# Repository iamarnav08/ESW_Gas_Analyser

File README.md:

# ESW-Beyond_Infinity

ESW Project

## Working of MQ 2 sensor

Gases - LPG , CO , smoke

Concentration -> 30 - 500 ppm

Donor atoms (or oxygen vacancies) provide free electrons that can conduct electricity in the tin dioxide.
When the sensor is exposed to air, oxygen gets adsorbed on the surface and traps these donor electrons, reducing conductivity (increasing resistance).
When reducing gases (like methane or CO) are present, they react with the adsorbed oxygen, freeing the donor electrons and increasing the conductivity (lowering resistance).
The sensor measures these changes in resistance (conductivity), and the output voltage increases with the gas concentration because more electrons are available to flow as current.

## Working of MQ7 sensor

The MQ-7 sensor is designed to detect carbon monoxide (CO) using a tin dioxide (SnO₂) sensing element. It works by changing its electrical resistance when CO is present. In clean air, the sensor has high resistance, but when CO interacts with the SnO₂ surface, the resistance decreases.

A key feature of the MQ-7 is its cyclic heating process:

At high temperature (320°C), the sensor cleans itself by adsorbing oxygen molecules.
At low temperature (100°C), the sensor becomes sensitive to CO, reducing its resistance in the presence of CO.
The sensor outputs an analog signal proportional to the CO concentration, making it ideal for CO detectors due to its improved accuracy and selectivity.

## Specialized for CO Detection

MQ-7 is specifically designed to detect carbon monoxide (CO) with high sensitivity. It is fine-tuned through its cyclic heating process, which improves its selectivity for CO and helps reduce interference from other gases. The MQ-7 sensor employs a cyclic heating process, alternating between a high temperature (for cleaning) and a low temperature (for CO detection). This process makes the MQ-7 more selective to CO, reducing false positives from other gases like hydrogen or methane.
The MQ-7 sensor operates on a cyclic heating mechanism with two distinct temperature phases:

High-temperature phase (around 300°C to 350°C): During this phase, the sensor burns off impurities or other gases that may have adsorbed on the surface, ensuring that it is primed for CO detection.
Low-temperature phase (around 100°C to 150°C): This lower temperature is where CO is effectively detected. At this temperature, the CO molecules are adsorbed onto the SnO₂ surface, triggering the redox reaction and thus leading to a measurable change in resistance.

This temperature cycling is essential because it optimizes the sensor's selectivity for CO while minimizing interference from other gases.
Change in Electrical Resistance

## Change in electrical Resistance

As CO is oxidized on the SnO₂ surface, oxygen molecules that were previously adsorbed on the surface as O⁻ ions are released, leading to a reduction in the number of charge carriers trapped on the surface.
This release of oxygen increases the availability of free electrons in the SnO₂ material, leading to a decrease in resistance.
The change in resistance is directly proportional to the concentration of CO in the surrounding air, allowing the sensor to measure CO levels.

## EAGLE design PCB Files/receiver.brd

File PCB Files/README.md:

PCBs designed for this product.

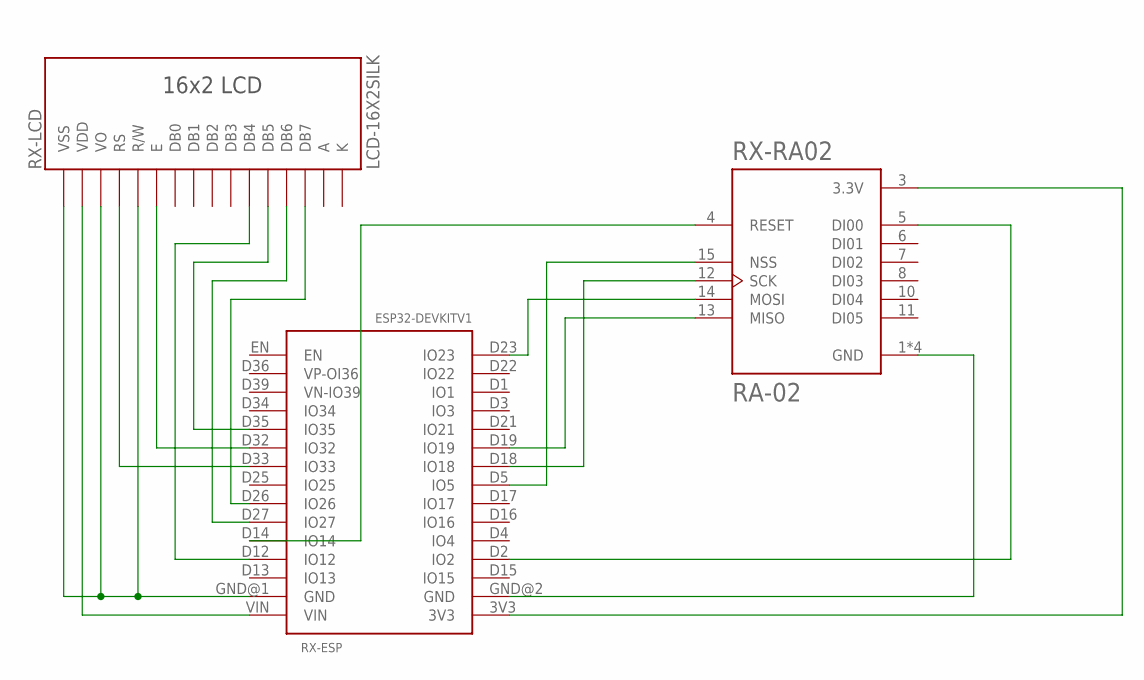
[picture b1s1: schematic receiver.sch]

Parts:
RX-ESP: ESP32DEVKITV1; ESP32-DEVKITV1
RX-LCD: LCD-16X2SILK; MODULE_LCD-16X2
RX-RA02: RA-02

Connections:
A: RX-LCD.15 (A)
K: RX-LCD.16 (K)
unnamed: RX-ESP.D23 (IO23), RX-RA02.14 (MOSI)
unnamed: RX-ESP.D2 (IO2), RX-RA02.5 (DI00)
unnamed: RX-ESP.GND@2 (GND), RX-RA02.1 (GND), RX-RA02.2 (GND), RX-RA02.9 (GND), RX-RA02.16 (GND)
unnamed: RX-ESP.D19 (IO19), RX-RA02.13 (MISO)
unnamed: RX-ESP.D18 (IO18), RX-RA02.12 (SCK)
unnamed: RX-ESP.D5 (IO5), RX-RA02.15 (NSS)
unnamed: RX-ESP.D14 (IO14), RX-RA02.4 (RESET)
unnamed: RX-ESP.3V3, RX-RA02.3 (3.3V)
unnamed: RX-ESP.VIN, RX-LCD.2 (VDD)
unnamed: RX-ESP.D32 (IO32), RX-LCD.6 (E)
unnamed: RX-ESP.D33 (IO33), RX-LCD.4 (RS)
unnamed: RX-ESP.D27 (IO27), RX-LCD.13 (DB6)
unnamed: RX-ESP.D35 (IO35), RX-LCD.12 (DB5)
unnamed: RX-ESP.D12 (IO12), RX-LCD.11 (DB4)
RX-N$1: RX-ESP.D26 (IO26), RX-LCD.14 (DB7)
RX-N$4: RX-ESP.GND@1 (GND), RX-LCD.1 (VSS), RX-LCD.3 (VO), RX-LCD.5 (R/W)

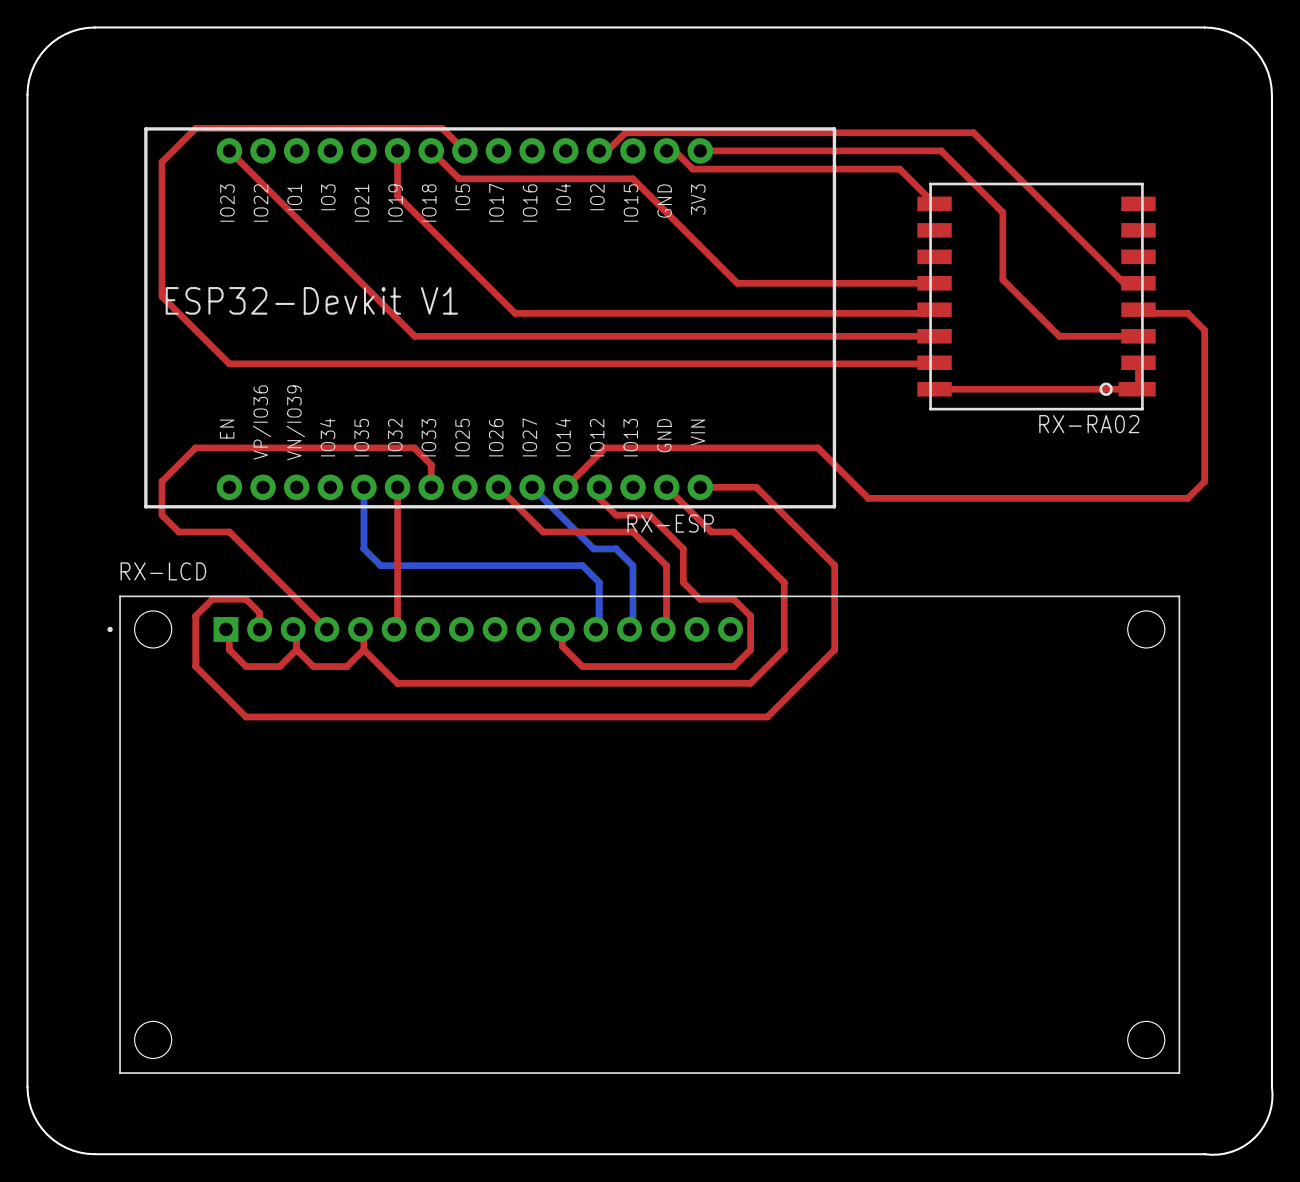
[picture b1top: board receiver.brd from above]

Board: 2 copper layers, 94.0 x 85.1 mm, 3 parts (0 on the bottom side), 16 nets.

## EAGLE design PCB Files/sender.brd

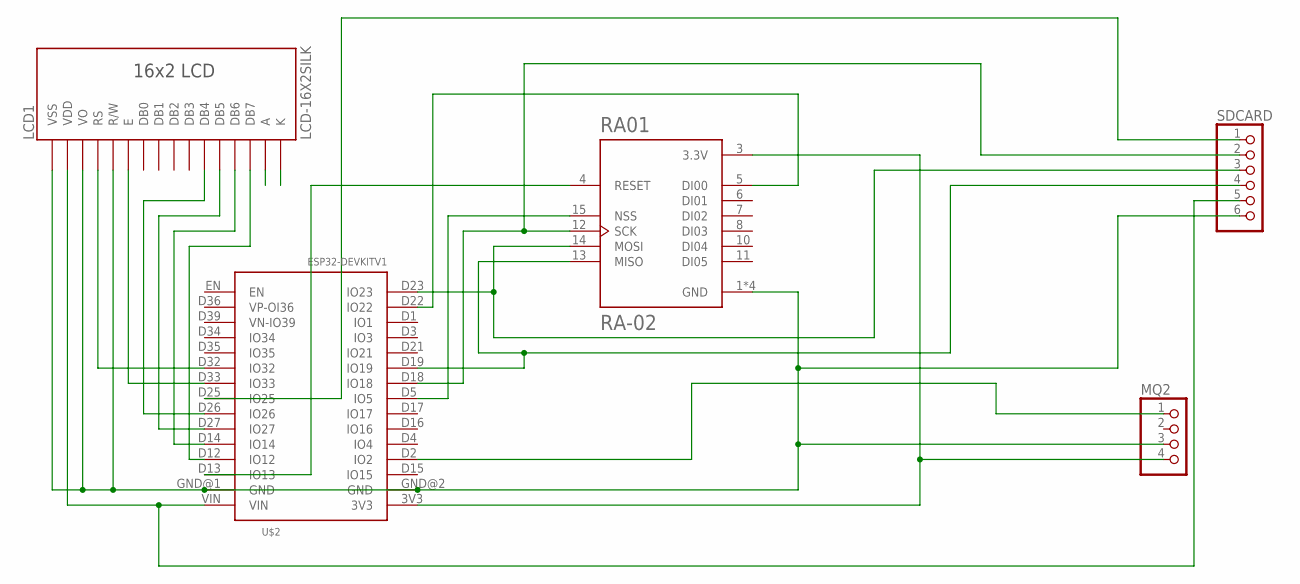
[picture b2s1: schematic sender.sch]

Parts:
LCD1: LCD-16X2SILK; MODULE_LCD-16X2
MQ2: PINHD-1X4; 1X04
RA01: RA-02
SDCARD: PINHD-1X6; 1X06
U$2: ESP32DEVKITV1; ESP32-DEVKITV1

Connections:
unnamed: RA01.4 (RESET), U$2.D13 (IO13)
unnamed: RA01.12 (SCK), SDCARD.2, U$2.D18 (IO18)
unnamed: RA01.15 (NSS), U$2.D5 (IO5)
unnamed: RA01.5 (DI00), U$2.D22 (IO22)
unnamed: RA01.13 (MISO), SDCARD.4, U$2.D19 (IO19)
unnamed: RA01.14 (MOSI), SDCARD.3, U$2.D23 (IO23)
unnamed: MQ2.4, RA01.3 (3.3V), U$2.3V3
unnamed: LCD1.1 (VSS), LCD1.3 (VO), LCD1.5 (R/W), MQ2.3, RA01.1 (GND), RA01.2 (GND), RA01.9 (GND), RA01.16 (GND), SDCARD.6, U$2.GND@1 (GND), U$2.GND@2 (GND)
unnamed: LCD1.14 (DB7), U$2.D12 (IO12)
unnamed: LCD1.13 (DB6), U$2.D14 (IO14)
unnamed: LCD1.12 (DB5), U$2.D27 (IO27)
unnamed: LCD1.11 (DB4), U$2.D26 (IO26)
unnamed: LCD1.2 (VDD), SDCARD.5, U$2.VIN
unnamed: LCD1.6 (E), U$2.D33 (IO33)
unnamed: LCD1.4 (RS), U$2.D32 (IO32)
unnamed: MQ2.1, U$2.D2 (IO2)
unnamed: SDCARD.1, U$2.D25 (IO25)

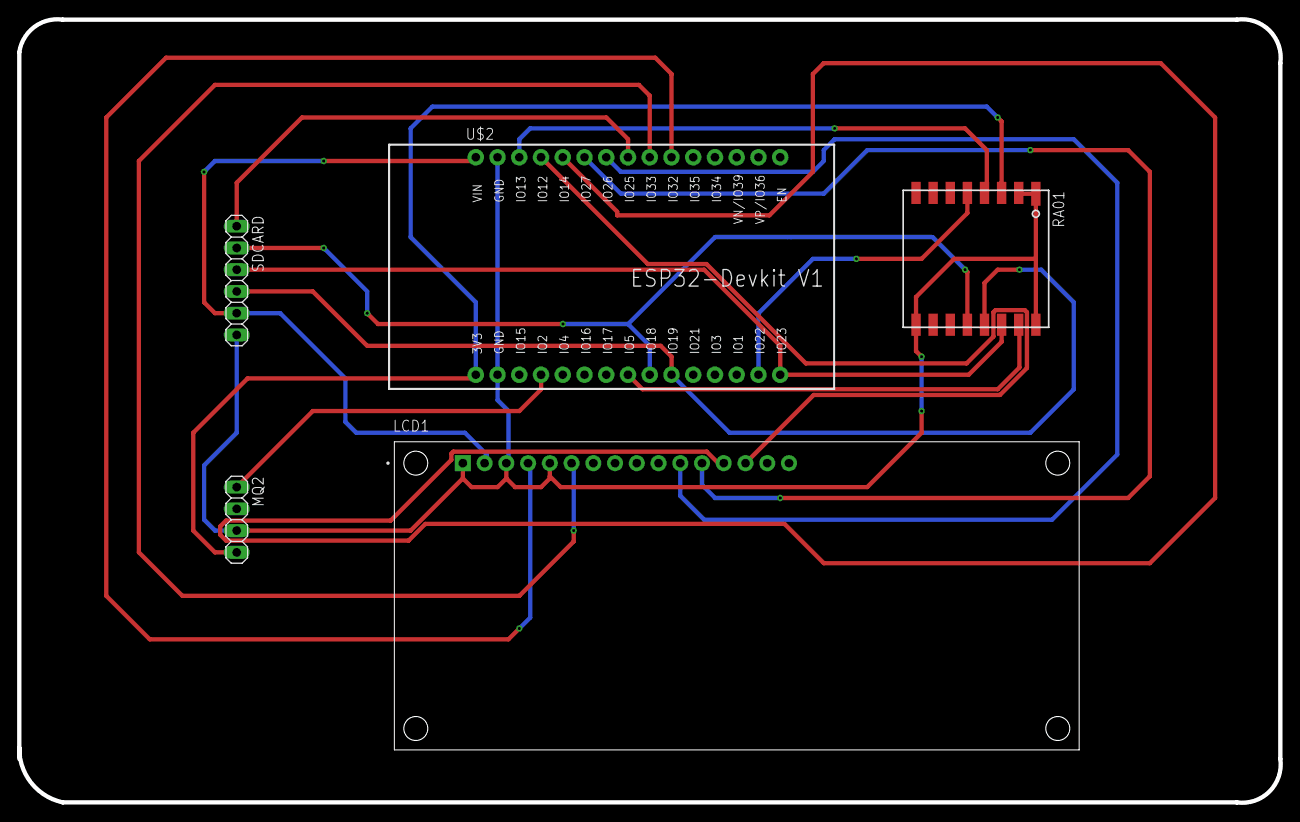
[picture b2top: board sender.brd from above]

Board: 2 copper layers, 147.4 x 91.5 mm, 5 parts (0 on the bottom side), 17 nets.
